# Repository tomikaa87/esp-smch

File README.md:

# esp-smch
ESP8266-based version of Shutter Motor Controller Hub

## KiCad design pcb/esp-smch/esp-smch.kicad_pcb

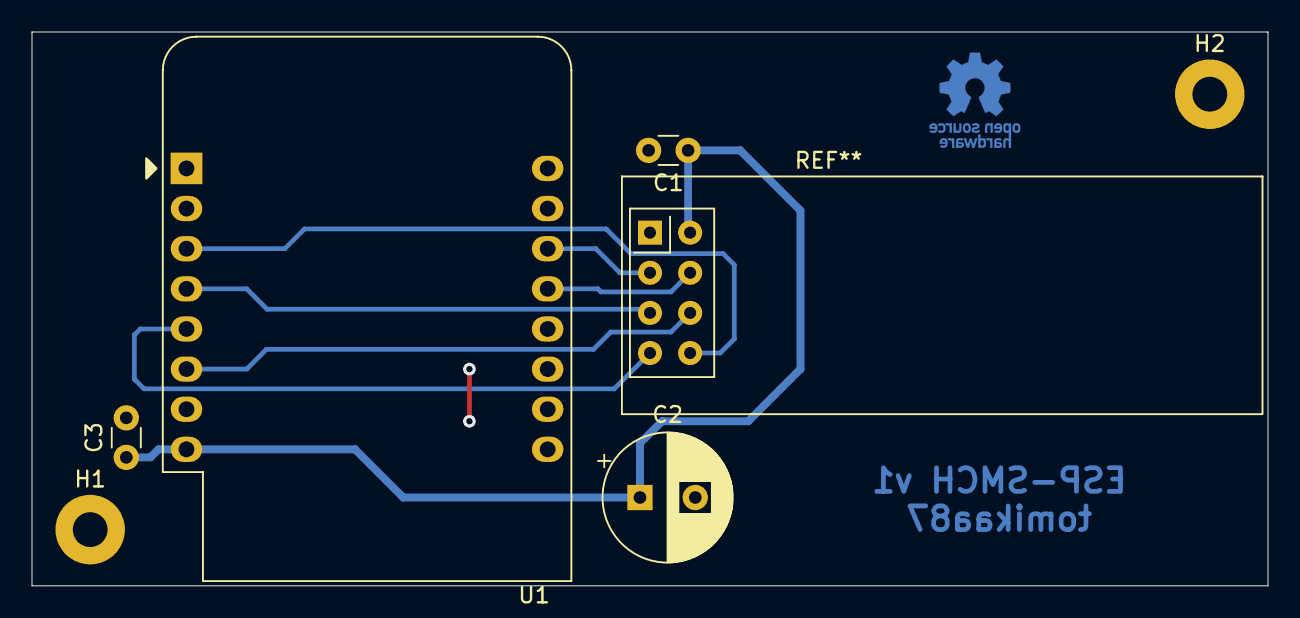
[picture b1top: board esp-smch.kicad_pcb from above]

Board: 2 copper layers, 78.2 x 35.1 mm, 8 parts (1 on the bottom side), 8 nets.

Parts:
C1, C3: 100n; C_Disc_D3.0mm_W1.6mm_P2.50mm
C2: 1000u; CP_Radial_D8.0mm_P3.50mm
H1, H2: MountingHole; MountingHole_2.2mm_M2_Pad
LOGO1: Logo_Open_Hardware_Small; OSHW-Logo_5.7x6mm_Copper
U1: WeMos_D1_mini; WEMOS_D1_mini_light
U2: NRF24L01_Breakout; NRF24L01P_PA_LNA_Breakout

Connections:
+3V3: C1.1, C2.1, C3.1, U1.8, U2.2
GND: C1.2, C2.2, C3.2, U1.10, U2.1
unnamed: U1.3, U2.8
unnamed: U1.4, U2.5
unnamed: U1.5, U2.7
unnamed: U1.6, U2.6
unnamed: U1.13, U2.4
unnamed: U1.14, U2.3

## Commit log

2020-05-04 Ignore PrivateConfig.h
2020-05-04 Begin implementing DeviceHub
2020-05-04 Working device scanning
2020-08-18 Use esp-iot-base
2020-12-21 Implement basic functionality
2020-12-21 Update esp-iot-base
2020-12-21 Enable remote logging
2021-01-04 Support Arduino OTA password
2021-03-05 Read ArduinoOTA password from the environment
2021-03-05 Initial commit of PCB design
2021-03-18 PCB: use nRF24L01+ PA-LNA breakout board
2021-03-20 PCB: add missing library file
2021-03-20 PCB: new layout
2021-05-07 Implement web API for basic up/down commands
2021-05-07 Implement AllUp/AllDown command
2021-05-31 Add host name configuration option
2021-08-18 Update esp-iot-base, fix warnings, pin lib deps
2022-01-01 Implement MQTT support
2022-07-04 MQTT: add support for user/pass authentication
2022-08-05 Support Home Assistant automatic MQTT discovery
2022-08-05 Bump version of esp-iot-base
2022-08-05 Fully disable Blynk-related code when needed
2022-08-06 Optimize memory usage of HA MQTT configs
2022-08-07 Disable periodic HTTP update check by default
2022-11-02 Update the espressif framework, free up some RAM, disable HTTP OTA update
2022-11-02 Free up some more RAM
